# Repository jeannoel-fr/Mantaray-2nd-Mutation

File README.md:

# Mantaray-2nd-Mutation

Evolution of Mantaray Mutation :

- 20° instead of 15°
- report all the num row on 2 rows on left hand,
- report dedicated shift and ctrl keys on left hand
- no hotplug on this one

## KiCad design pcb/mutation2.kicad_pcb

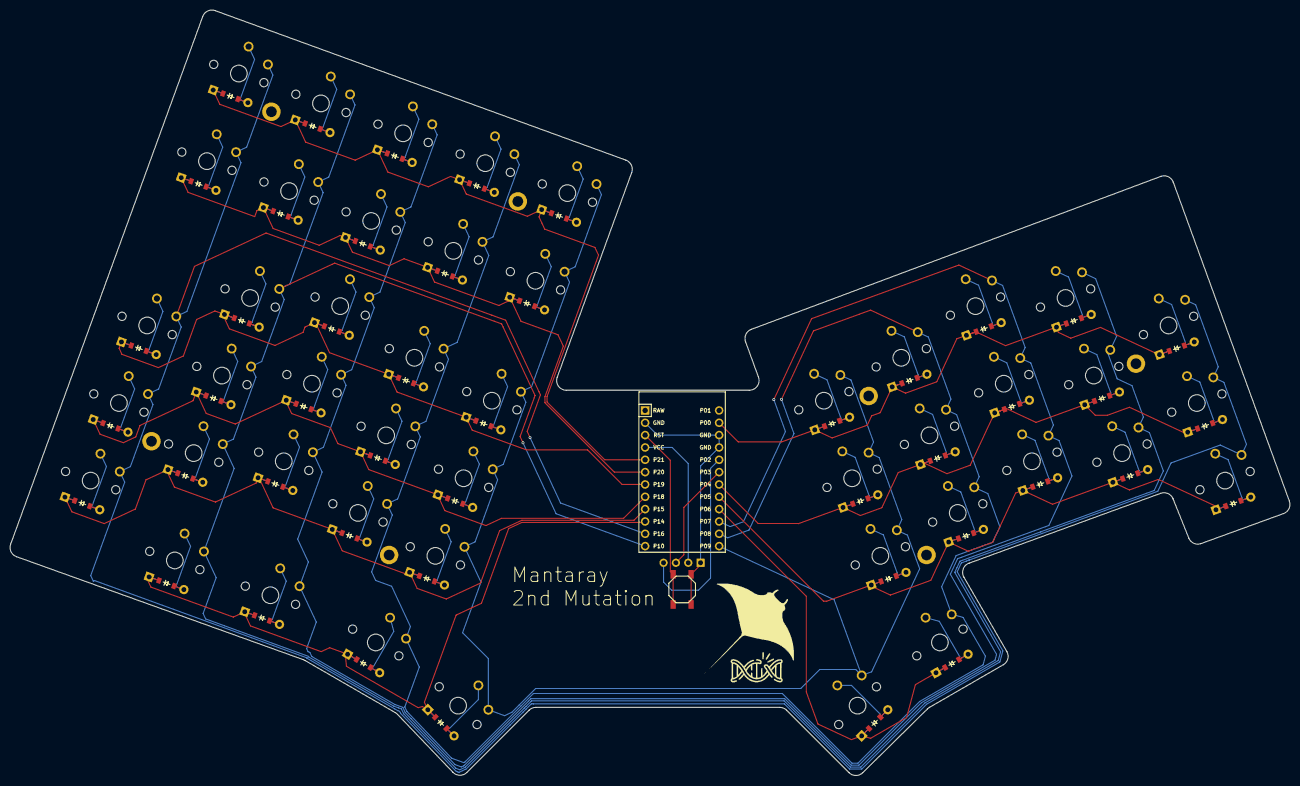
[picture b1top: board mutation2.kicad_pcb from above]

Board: 2 copper layers, 263.6 x 157.6 mm, 102 parts (0 on the bottom side), 66 nets.

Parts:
B1: SW_TACT_ALPS_SKQGABE010
D1, D2, D3, D4, D5, D6, D7, D8, D9, D10, D11, D12, D13, D14, D15, D16, D17, D18, D19, D20, D21, D22, D23, D24, D25, D26, D27, D28, D29, D30, D31, D32, D33, D34, D35, D36, D37, D38, D39, D40, D41, D42, D43, D44, D45, D46: ComboDiode
H1, H2, H3, H4, H5, H6, H7: mounting_hole_plated
MCU1: ProMicro
OLED1: OLED; OLED_headers
S1, S2, S3, S4, S5, S6, S7, S8, S9, S10, S11, S12, S13, S14, S15, S16, S17, S18, S19, S20, S21, S22, S23, S24, S25, S26, S27, S28, S29, S30, S31, S32, S33, S34, S35, S36, S37, S38, S39, S40, S41, S42, S43, S44, S45, S46: PG1350

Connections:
GND: B1.1, MCU1.2, MCU1.15, MCU1.16, OLED1.1
P0: D32.1, D35.1, D38.1, D41.1, D44.1, MCU1.14
P2: MCU1.17, OLED1.4
P3: MCU1.18, OLED1.3
P4: D31.1, D34.1, D37.1, D40.1, D43.1, MCU1.19
P5: D30.1, D33.1, D36.1, D39.1, D42.1, MCU1.20
P6: D45.1, D46.1, MCU1.21
P7: MCU1.22, S7.1, S8.1, S9.1, S20.1, S21.1, S27.1, S36.1, S37.1, S38.1
P8: MCU1.23, S10.1, S11.1, S12.1, S22.1, S23.1, S28.1, S39.1, S40.1, S41.1, S45.1
P9: MCU1.24, S13.1, S14.1, S15.1, S24.1, S25.1, S29.1, S42.1, S43.1, S44.1, S46.1
P10: MCU1.12, S4.1, S5.1, S6.1, S18.1, S19.1, S26.1, S33.1, S34.1, S35.1
P14: D26.1, D27.1, D28.1, D29.1, MCU1.10
P15: D1.1, D4.1, D7.1, D10.1, D13.1, MCU1.9
P16: MCU1.11, S1.1, S2.1, S3.1, S16.1, S17.1, S30.1, S31.1, S32.1
P18: D2.1, D5.1, D8.1, D11.1, D14.1, MCU1.8
P19: D3.1, D6.1, D9.1, D12.1, D15.1, MCU1.7
P20: D16.1, D18.1, D20.1, D22.1, D24.1, MCU1.6
P21: D17.1, D19.1, D21.1, D23.1, D25.1, MCU1.5
RST: B1.2, MCU1.3
VCC: MCU1.4, OLED1.2
ctrl_cluster: D27.2, S27.2
index_bottom: D10.2, S10.2
index_home: D11.2, S11.2
index_num: D22.2, S22.2
index_num2: D23.2, S23.2
index_top: D12.2, S12.2
inner_bottom: D13.2, S13.2
inner_home: D14.2, S14.2
inner_num: D24.2, S24.2
inner_num2: D25.2, S25.2
inner_top: D15.2, S15.2
layer_cluster: D28.2, S28.2
middle_bottom: D7.2, S7.2
middle_home: D8.2, S8.2
middle_num: D20.2, S20.2
middle_num2: D21.2, S21.2
middle_top: D9.2, S9.2
mirror_index_bottom: D39.2, S39.2
mirror_index_home: D40.2, S40.2
mirror_index_top: D41.2, S41.2
mirror_inner_bottom: D42.2, S42.2
mirror_inner_home: D43.2, S43.2
mirror_inner_top: D44.2, S44.2
mirror_layer_cluster: D45.2, S45.2
mirror_middle_bottom: D36.2, S36.2
mirror_middle_home: D37.2, S37.2
mirror_middle_top: D38.2, S38.2
mirror_pinky_bottom: D30.2, S30.2
mirror_pinky_home: D31.2, S31.2
mirror_pinky_top: D32.2, S32.2
mirror_ring_bottom: D33.2, S33.2
mirror_ring_home: D34.2, S34.2
mirror_ring_top: D35.2, S35.2
mirror_space_cluster: D46.2, S46.2
pinky_bottom: D1.2, S1.2
pinky_home: D2.2, S2.2
pinky_num: D16.2, S16.2
pinky_num2: D17.2, S17.2
pinky_top: D3.2, S3.2
ring_bottom: D4.2, S4.2
ring_home: D5.2, S5.2
ring_num: D18.2, S18.2
ring_num2: D19.2, S19.2
ring_top: D6.2, S6.2
shift_cluster: D26.2, S26.2
space_cluster: D29.2, S29.2

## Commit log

2025-04-25 initial push
